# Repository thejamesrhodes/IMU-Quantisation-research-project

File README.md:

# Sheppard MEMS Rate-Register Quantisation Research Project

Custom STM32F723 hardware, firmware and analysis for measuring output-register
quantisation noise in MEMS rate gyroscopes. Specifically gyroscopes that report an
angular-rate register rather than an integrated angle increment.

*This is a pre-publication research project. The preprint is not yet released.
the results, figures and numbers in this repository are working values and are subject to change. 
Nothing here has been peer-reviewed. Preliminary Datasets are available on Zenodo*

---

## Claim

Rate-register quantisation is predicted to appear at a $-1/2$ Allan-deviation
slope and to be absorbed silently into the fitted angle random walk (ARW),
rather than appearing as the $-1$-slope angle-quantisation ("Q") term of IEEE
Std 952, which describes a different output architecture for angle-increment
parts (FOGs, RLGs). This holds regardless of the error's statistics: whether the
quantisation error is PQN-white, deadbanded, or dithered, it enters the rate
and therefore appears inside the fitted ARW instead of appearing as a separable Q.

If that is correct, fitted stochastic-noise parameters depend on the
configuration (output data rate (ODR), full-scale range (FSR), output word
length) at which they were measured, and the $\sqrt{\text{ODR}}$
bandwidth-transfer rule embedded in every mainstream IMU calibration toolchain,
where it is stated as a condition requiring ideal decimation rather than a
validated result, has never been checked for modern high-ODR consumer parts.

**Why this has gone unnoticed.** The transfer rule was safe for the parts it was
developed on. An MPU-6050-class gyro (≈5 mdps/√Hz, 2011) at ±2000 dps / 100 Hz
sits at a dither ratio $\rho = \sigma/\Delta \approx 0.58$, where the
pseudo-quantisation-noise (PQN) model is valid to ~2 %. The ICM-42688-P
(≈2.8 mdps/√Hz, 2020) sits at $\rho \approx 0.32$, where it is not.

The board is named after W. F. Sheppard, whose 1898 paper gave the $-c^2/12$
correction for the variance of grouped data
([DOI](https://doi.org/10.1112/plms/s1-29.1.353)) - the same $\Delta^2/12$ the
whole experiment turns on. The correction reappears in an unexpected place: the
19-bit reference stream is itself a quantiser, and Sheppard's correction must be
applied to it before it can serve as a reference at all.

---

## Project Goals

- Test whether the fitted stochastic-noise parameters of a MEMS IMU transfer
  across ODR and FSR, and return a single configuration-invariant parameter set
  that does.
- Establish that rate-register quantisation presents at the $-1/2$ slope and is
  absorbed into the fitted ARW, distinct from the IEEE-952 angle-quantisation
  term.
- Derive the exact, parameter-free output-quantisation behaviour, governed by
  two quantities: the dither ratio $\rho = \sigma/\Delta$ and the sub-LSB bias
  phase $\mu \bmod \Delta$. Both measurable from a static code histogram with
  no additional hardware.
- Identify which requantisation architecture the output register implements
  (undithered/PQN, truncation, RPDF- or TPDF-dithered) from output data alone,
  validated against bit-exact software-dithered controls.
- Show that no mainstream toolchain (Kalibr, `allan_variance_ros`, …) models
  output-register quantisation or exposes $\rho$ or $\mu$, and document the
  effect size against configuration so a practitioner can locate their own.
- Publish the hardware, firmware, analysis code and a raw-integer-code,
  temperature-logged dataset. A dataset that, on the searches conducted, does
  not currently exist, because public IMU datasets are distributed as calibrated
  floats and the calibration destroys the code lattice.

---

## Project progress

| Item | Status |
| --- | --- |
| Data-logger PCB (4× IMU) Bring up | ✅ Complete |
| Firmware | ✅ Complete |
| Analysis chain ($\sigma$, $\rho$, $\mu$, $\varphi$, $\eta$; Allan; GMWM) | ✅ Complete |
| Exact $\eta(\rho,\varphi)$ theory, closed form | ✅ Validated |
| Primary curve $\eta(\rho)$ | ✅ Measured over a decade of $\rho$ |
| Experimental results vs exact theory | ✅ 0.4 % of range, no free parameters, both specimens |
| Relevance evidence (toolchain guidance, default ODR/FSR) | 🚧 In progress |
| Manuscript | 🚧 Skeleton, not in this repository |
| Preprint | ⏳ Not yet released |

---

## Hardware

|           |                                                            |
| --------- | ---------------------------------------------------------- |
| MCU       | STM32F723ZET6, 32 MHz                                       |
| Sensors   | 2× ICM-42688-P, 1× ISM330DHCX, 1× BMI323, one SPI bus each |
| Storage   | microSD on SDMMC2, exFAT                                    |
| Host link | USB-C on OTG_HS, internal HS PHY                            |
| Power     | 4S NiMH or USB-C                                            |

---

## Repository structure

```
GMWM Software/                 STM32CubeIDE firmware project + host Python
  Core/                          application sources
  tools/                         console, analysis, figures
GMWM Electronics/              KiCad 10 — data-logger PCB
Array Electronics ICM42688P/   KiCad 10 — ICM-42688-P board
Array Software ICM42688P/      firmware for the ICM-42688-P board
Test Datasets/                 records (gitignored; archived to Zenodo)
zenodo/                        dataset deposit build system
```

---

## Running it

```
pip install pyserial numpy matplotlib
python "GMWM Software/tools/sheppard_console.py"
```

The console is a GUI with five tabs: a terminal, the SD-card browser, the
campaign-plan editor, an analysis runner, and a figure viewer that renders the
plots in-app. It finds the board by USB ID rather than COM port and reconnects
on its own when the board resets.

Everything it does is also available from the command line, and the panel prints
the exact command before it runs it, so a result in the GUI and a result in a
terminal are the same result.

```
python analyse.py summary "../../Test Datasets" -o "../../Test Datasets/summary.csv" --fast
python figures.py "../../Test Datasets/summary.csv" -o "../../Figures"
python offset_fit.py "../../Test Datasets" --glob "*ph_k*.sdat"
```

---

## Flashing without an ST-LINK

The board reflashes itself over the same USB-C cable that carries the console.

Run `sheppard_selftest.py` once before trusting the flasher. It feeds the board
bad data five ways and checks each one is refused with flash untouched. Nothing
in it can erase the board.

SWD recovery is always there:

```
STM32_Programmer_CLI -c port=SWD mode=UR -e all -w "Debug/GMWM STM32.elf" -v -rst
```

---

## Status

94 records, two specimens, three axes. The register's architecture is identified
(truncation, bit-exact); $\eta(\rho)$ is measured over a decade of $\rho$; and a
controlled phase sweep tracks the exact theory to **0.4 % of its range with no
free parameters — on both specimens independently**. Repeatability is measured
at $\sigma_\eta = 0.0065$, so the theory is good to about twice the noise floor
of the apparatus.

The manuscript is a skeleton and is not held in this repository. The bench
work the preprint needs is
done; what remains is desk work — the relevance evidence, the software-dither
sweep, and the writing.

---

## Preprint and data

The preprint is not yet released. A manuscript is in preparation and is
intended for submission to a measurement-science journal (IOP
*Measurement Science and Technology*); this section will carry the preprint DOI
when it is public.

Campaign data is archived to Zenodo and is not held in this repository:

> Rhodes, J. (2026). *Paired 16-bit and 19-bit output records from two
> ICM-42688-P MEMS gyroscopes across output-rate and sub-LSB bias-offset
> sweeps* [Data set]. Zenodo. <https://doi.org/10.5281/zenodo.22860515>

---

## Conventions

SI units. LaTeX for maths. Campaign data goes to Zenodo with a DOI, not into
this repository.

The gyroscope's high-resolution FIFO field is 20 bits wide, of which 19 are
significant at ±2000 °/s full scale — the field's least significant bit is
always zero. All resolutions in this repository and in the dataset are quoted
on the 19-bit convention, so the reference lattice step is $\Delta' = \Delta/8$
and the register word is `gyro19 >> 3`.

---

## Licence

MIT — see `LICENSE`. The dataset is licensed separately under CC-BY-4.0.

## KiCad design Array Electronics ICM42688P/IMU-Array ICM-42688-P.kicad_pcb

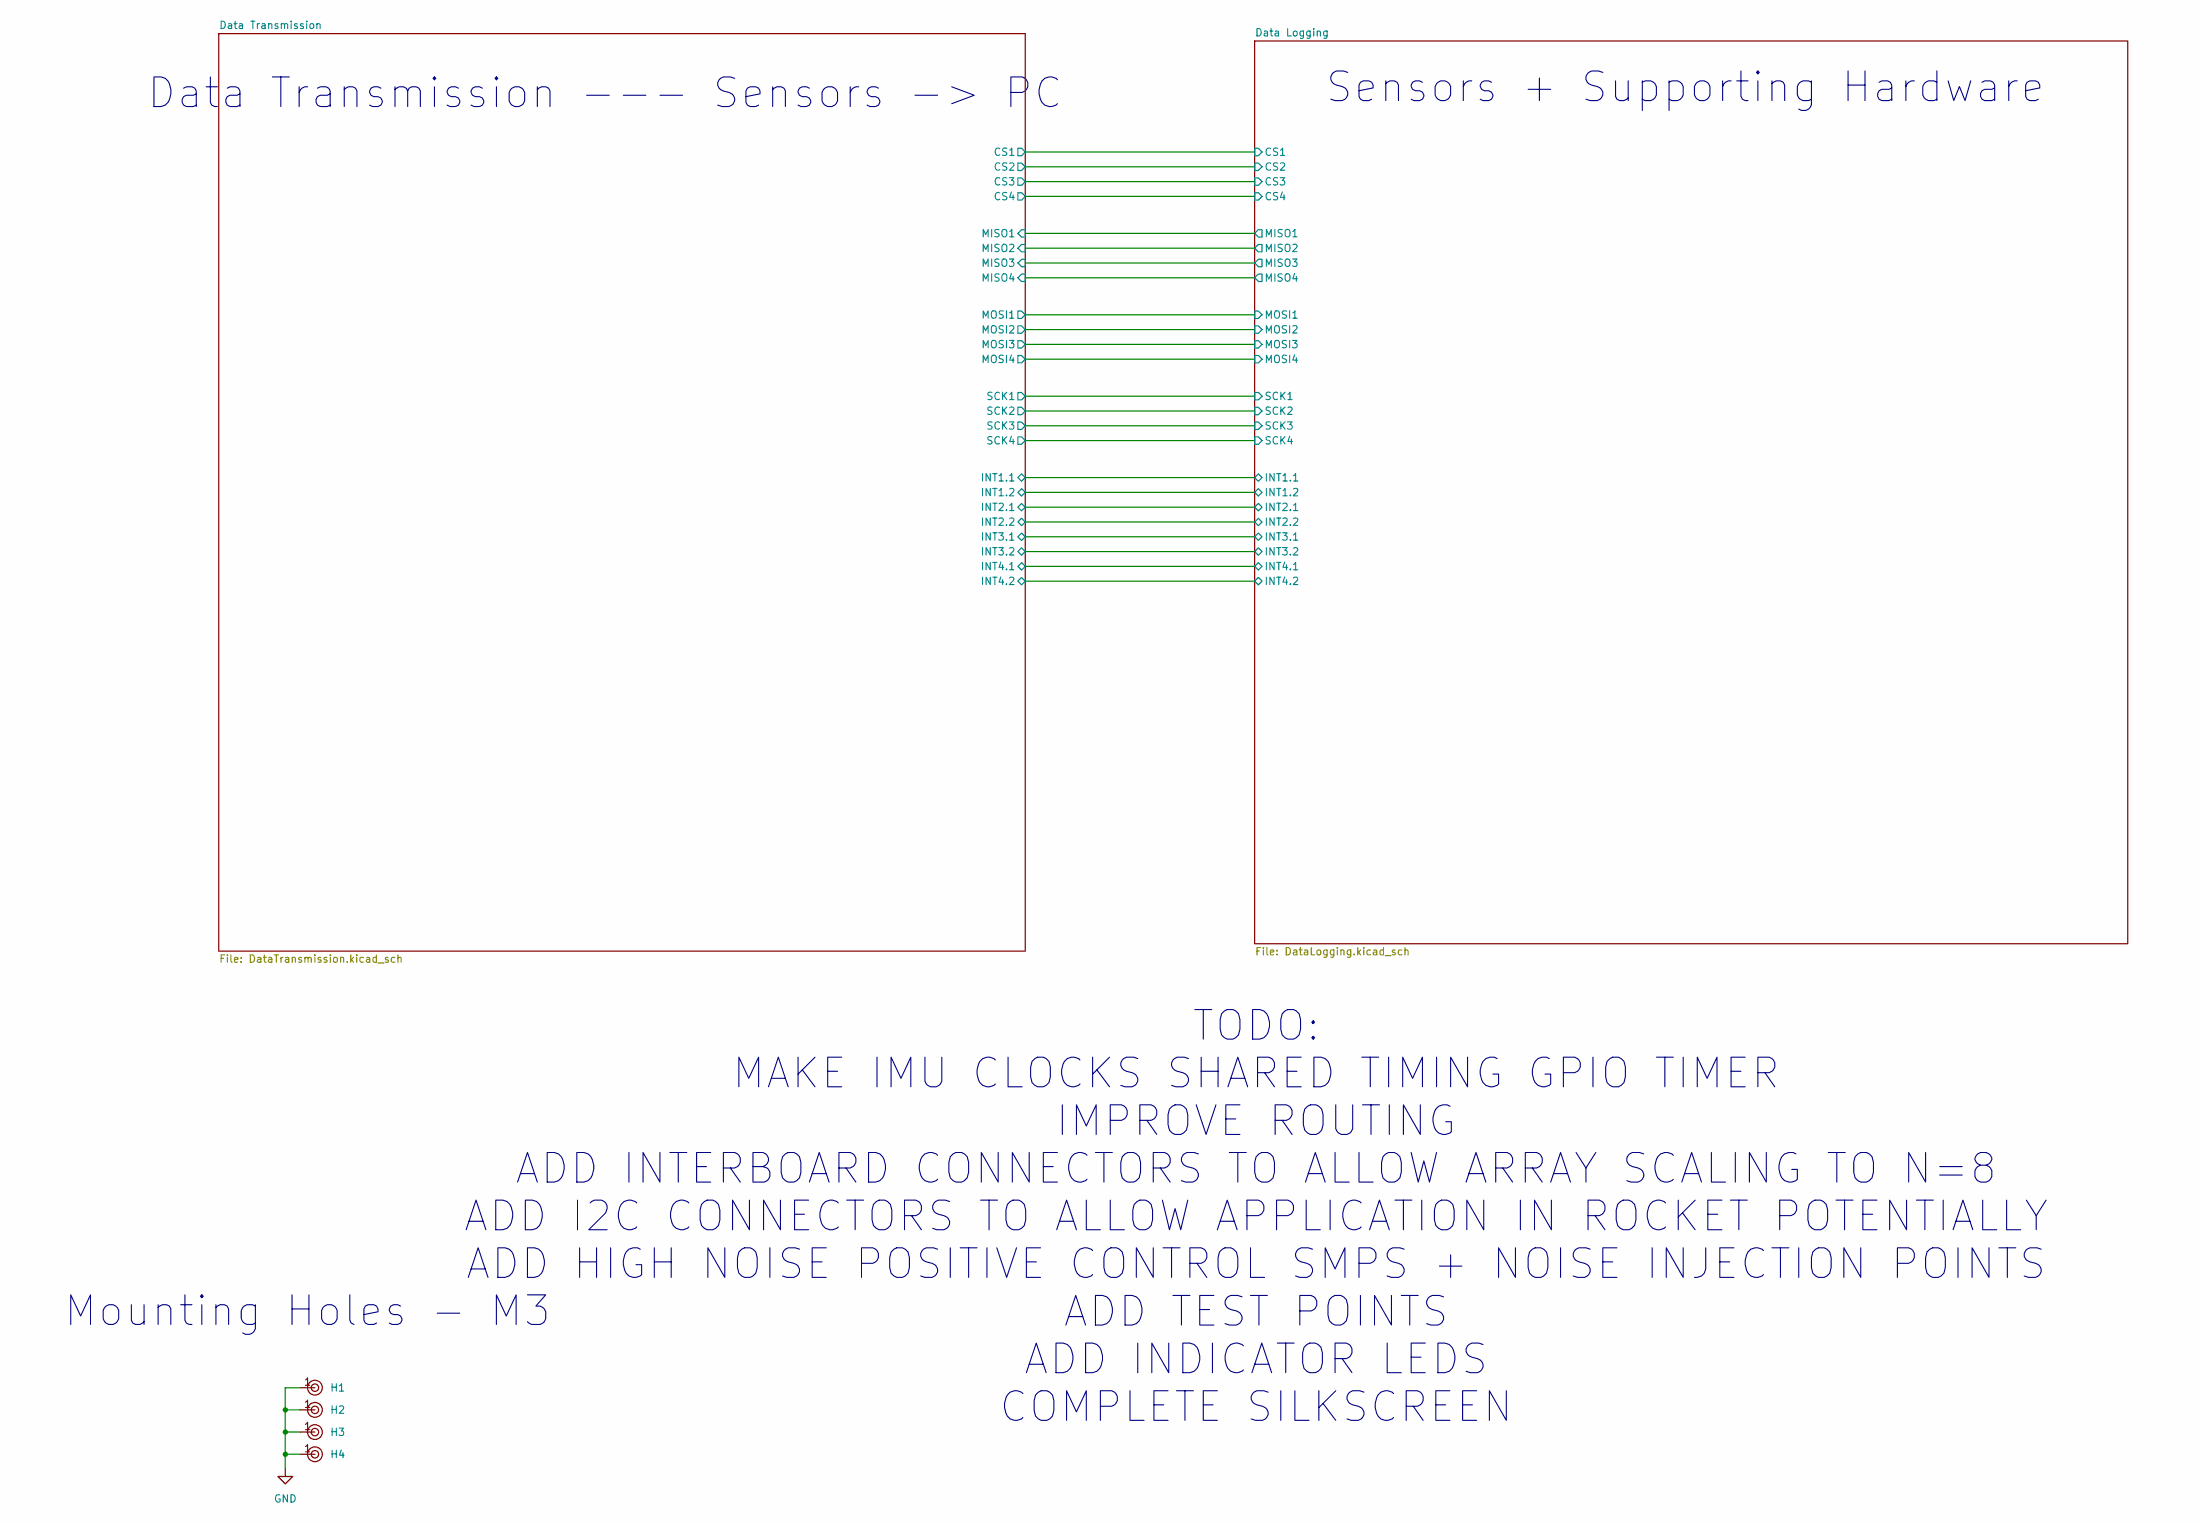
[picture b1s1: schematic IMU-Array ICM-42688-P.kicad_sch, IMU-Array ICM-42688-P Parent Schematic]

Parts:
H1, H2, H3, H4: Hole, 3mm

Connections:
GND: H1.1, H2.1, H3.1, H4.1; also elsewhere on the board

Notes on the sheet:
Sensors + Supporting Hardware
TODO: MAKE IMU CLOCKS SHARED TIMING GPIO TIMER IMPROVE ROUTING ADD INTERBOARD CONNECTORS TO ALLOW ARRAY SCALING TO N=8 ADD I2C CONNECTORS TO ALLOW APPLICATION IN ROCKET POTENTIALLY ADD HIGH NOISE POSITIVE CONTROL SMPS + NOISE INJECTION POINTS ADD TEST POINTS ADD INDICATOR LEDS COMPLETE SILKSCREEN
Data Transmission --- Sensors -> PC
Mounting Holes - M3

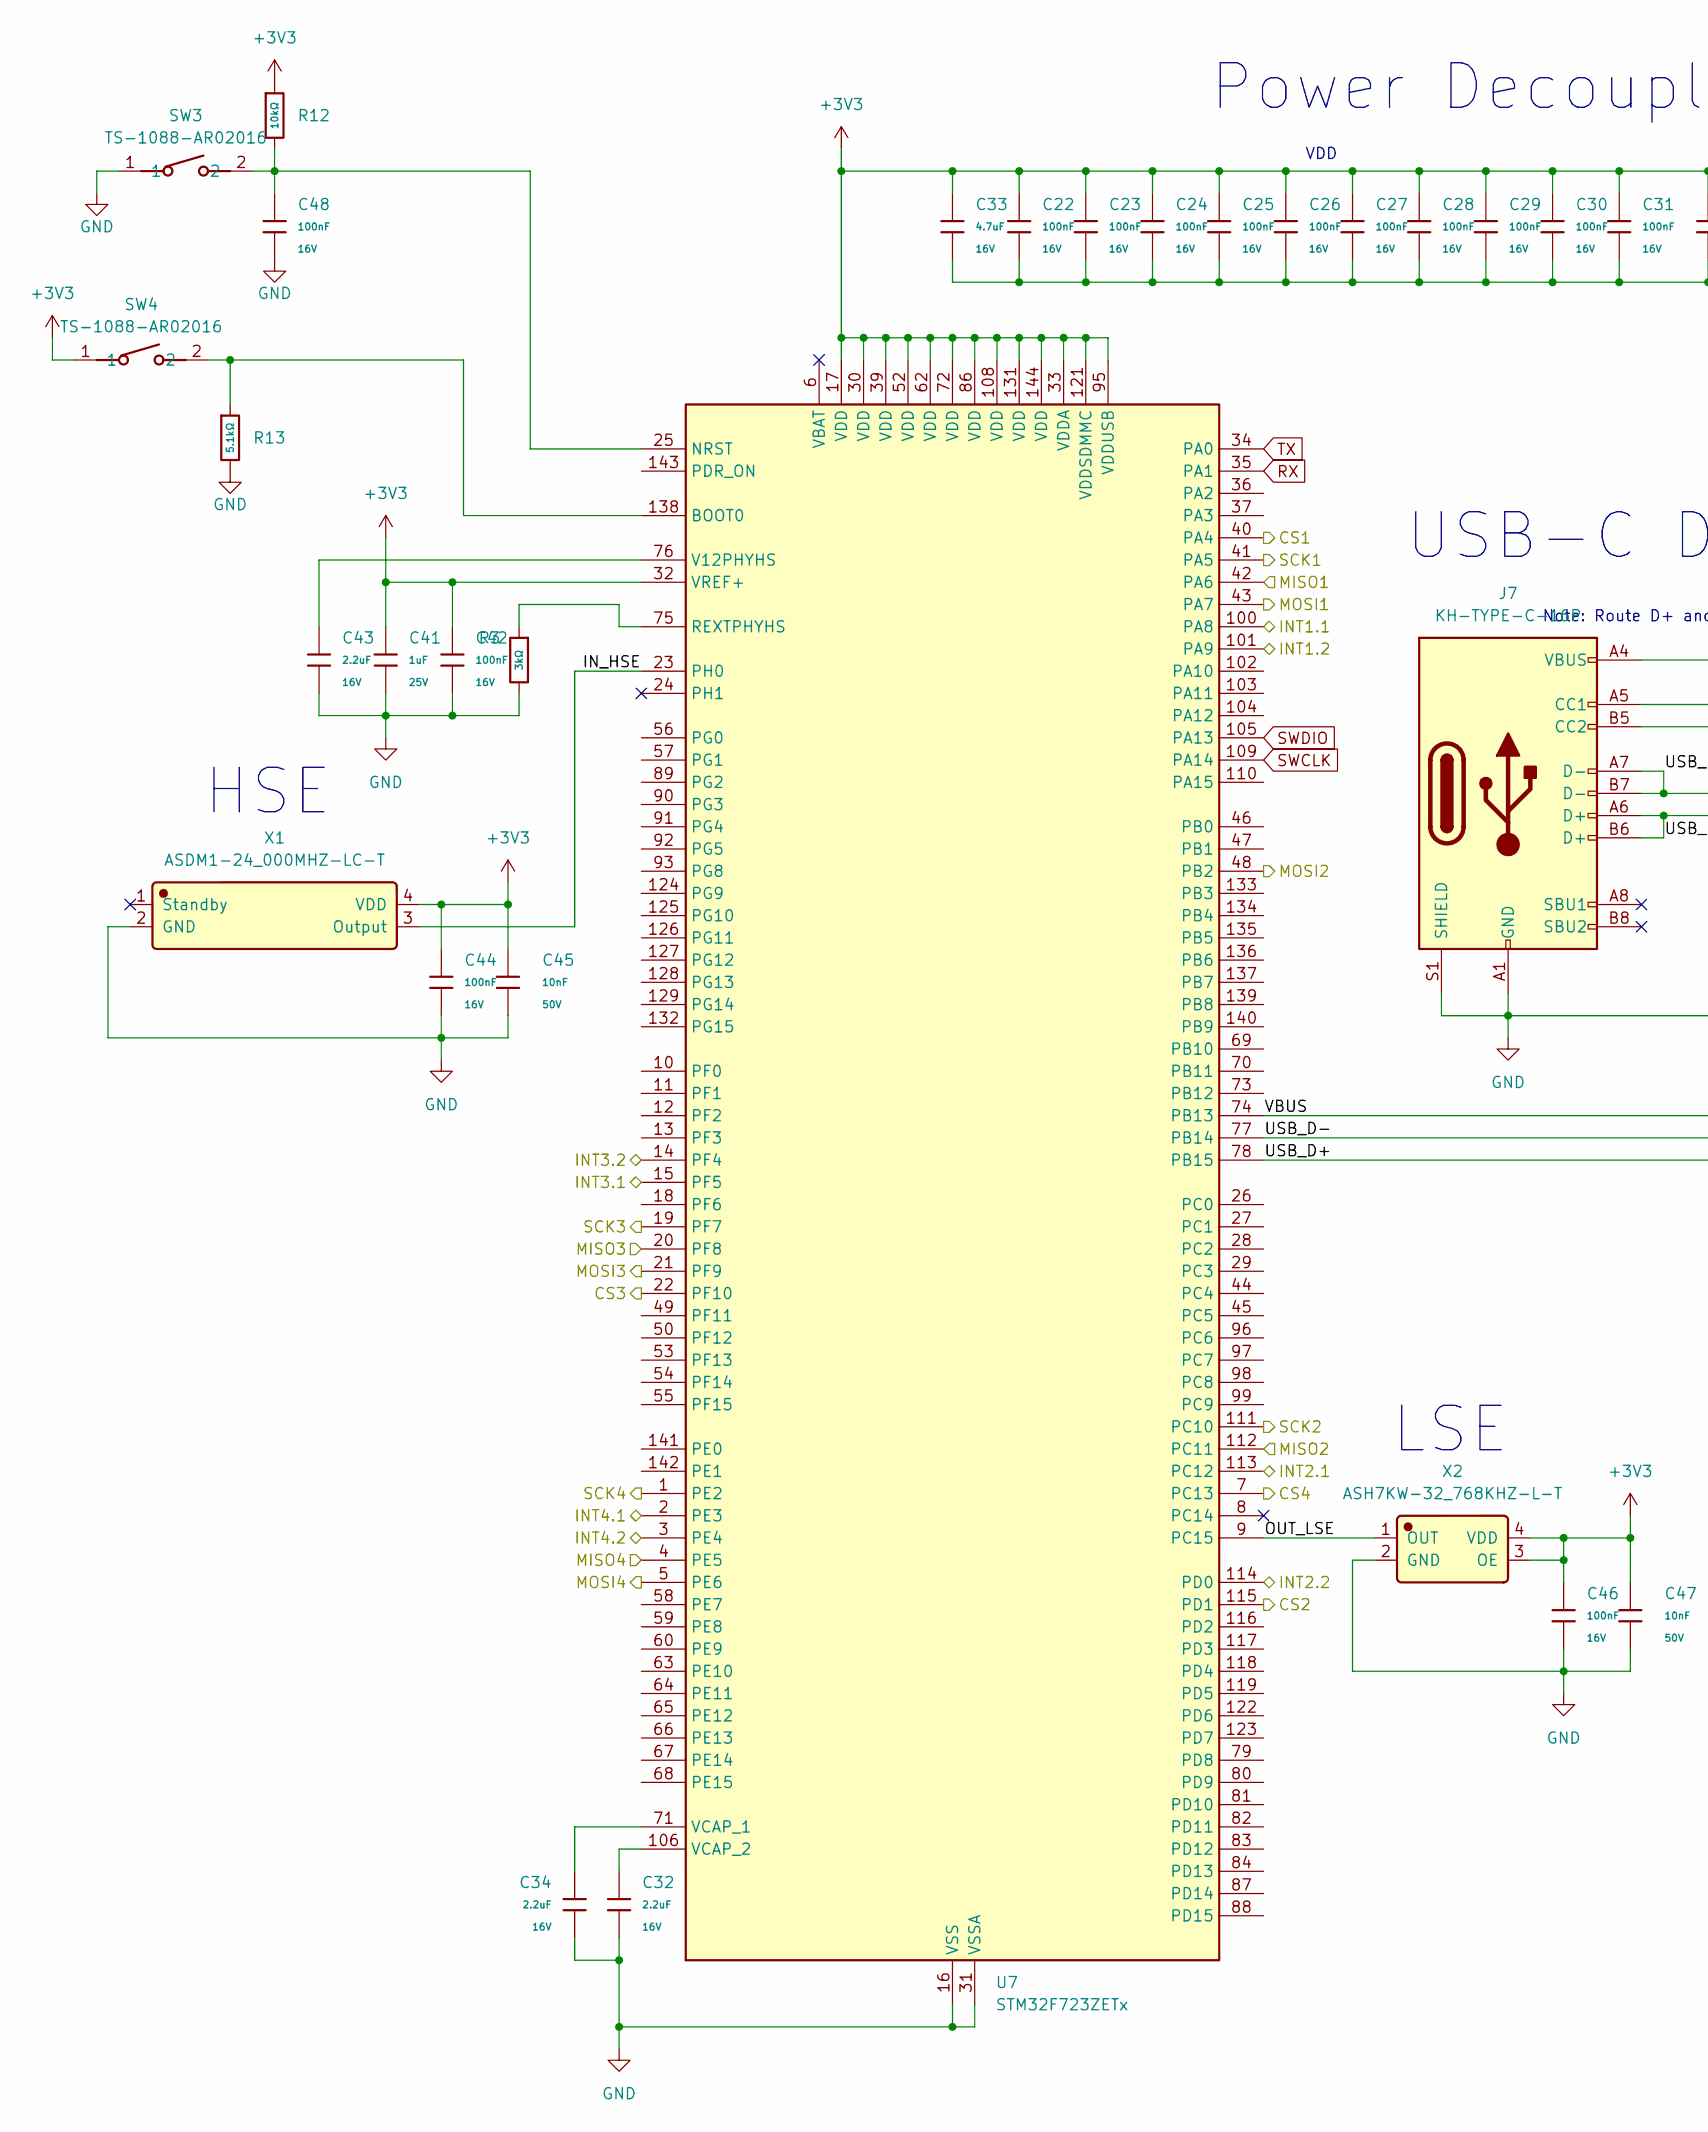
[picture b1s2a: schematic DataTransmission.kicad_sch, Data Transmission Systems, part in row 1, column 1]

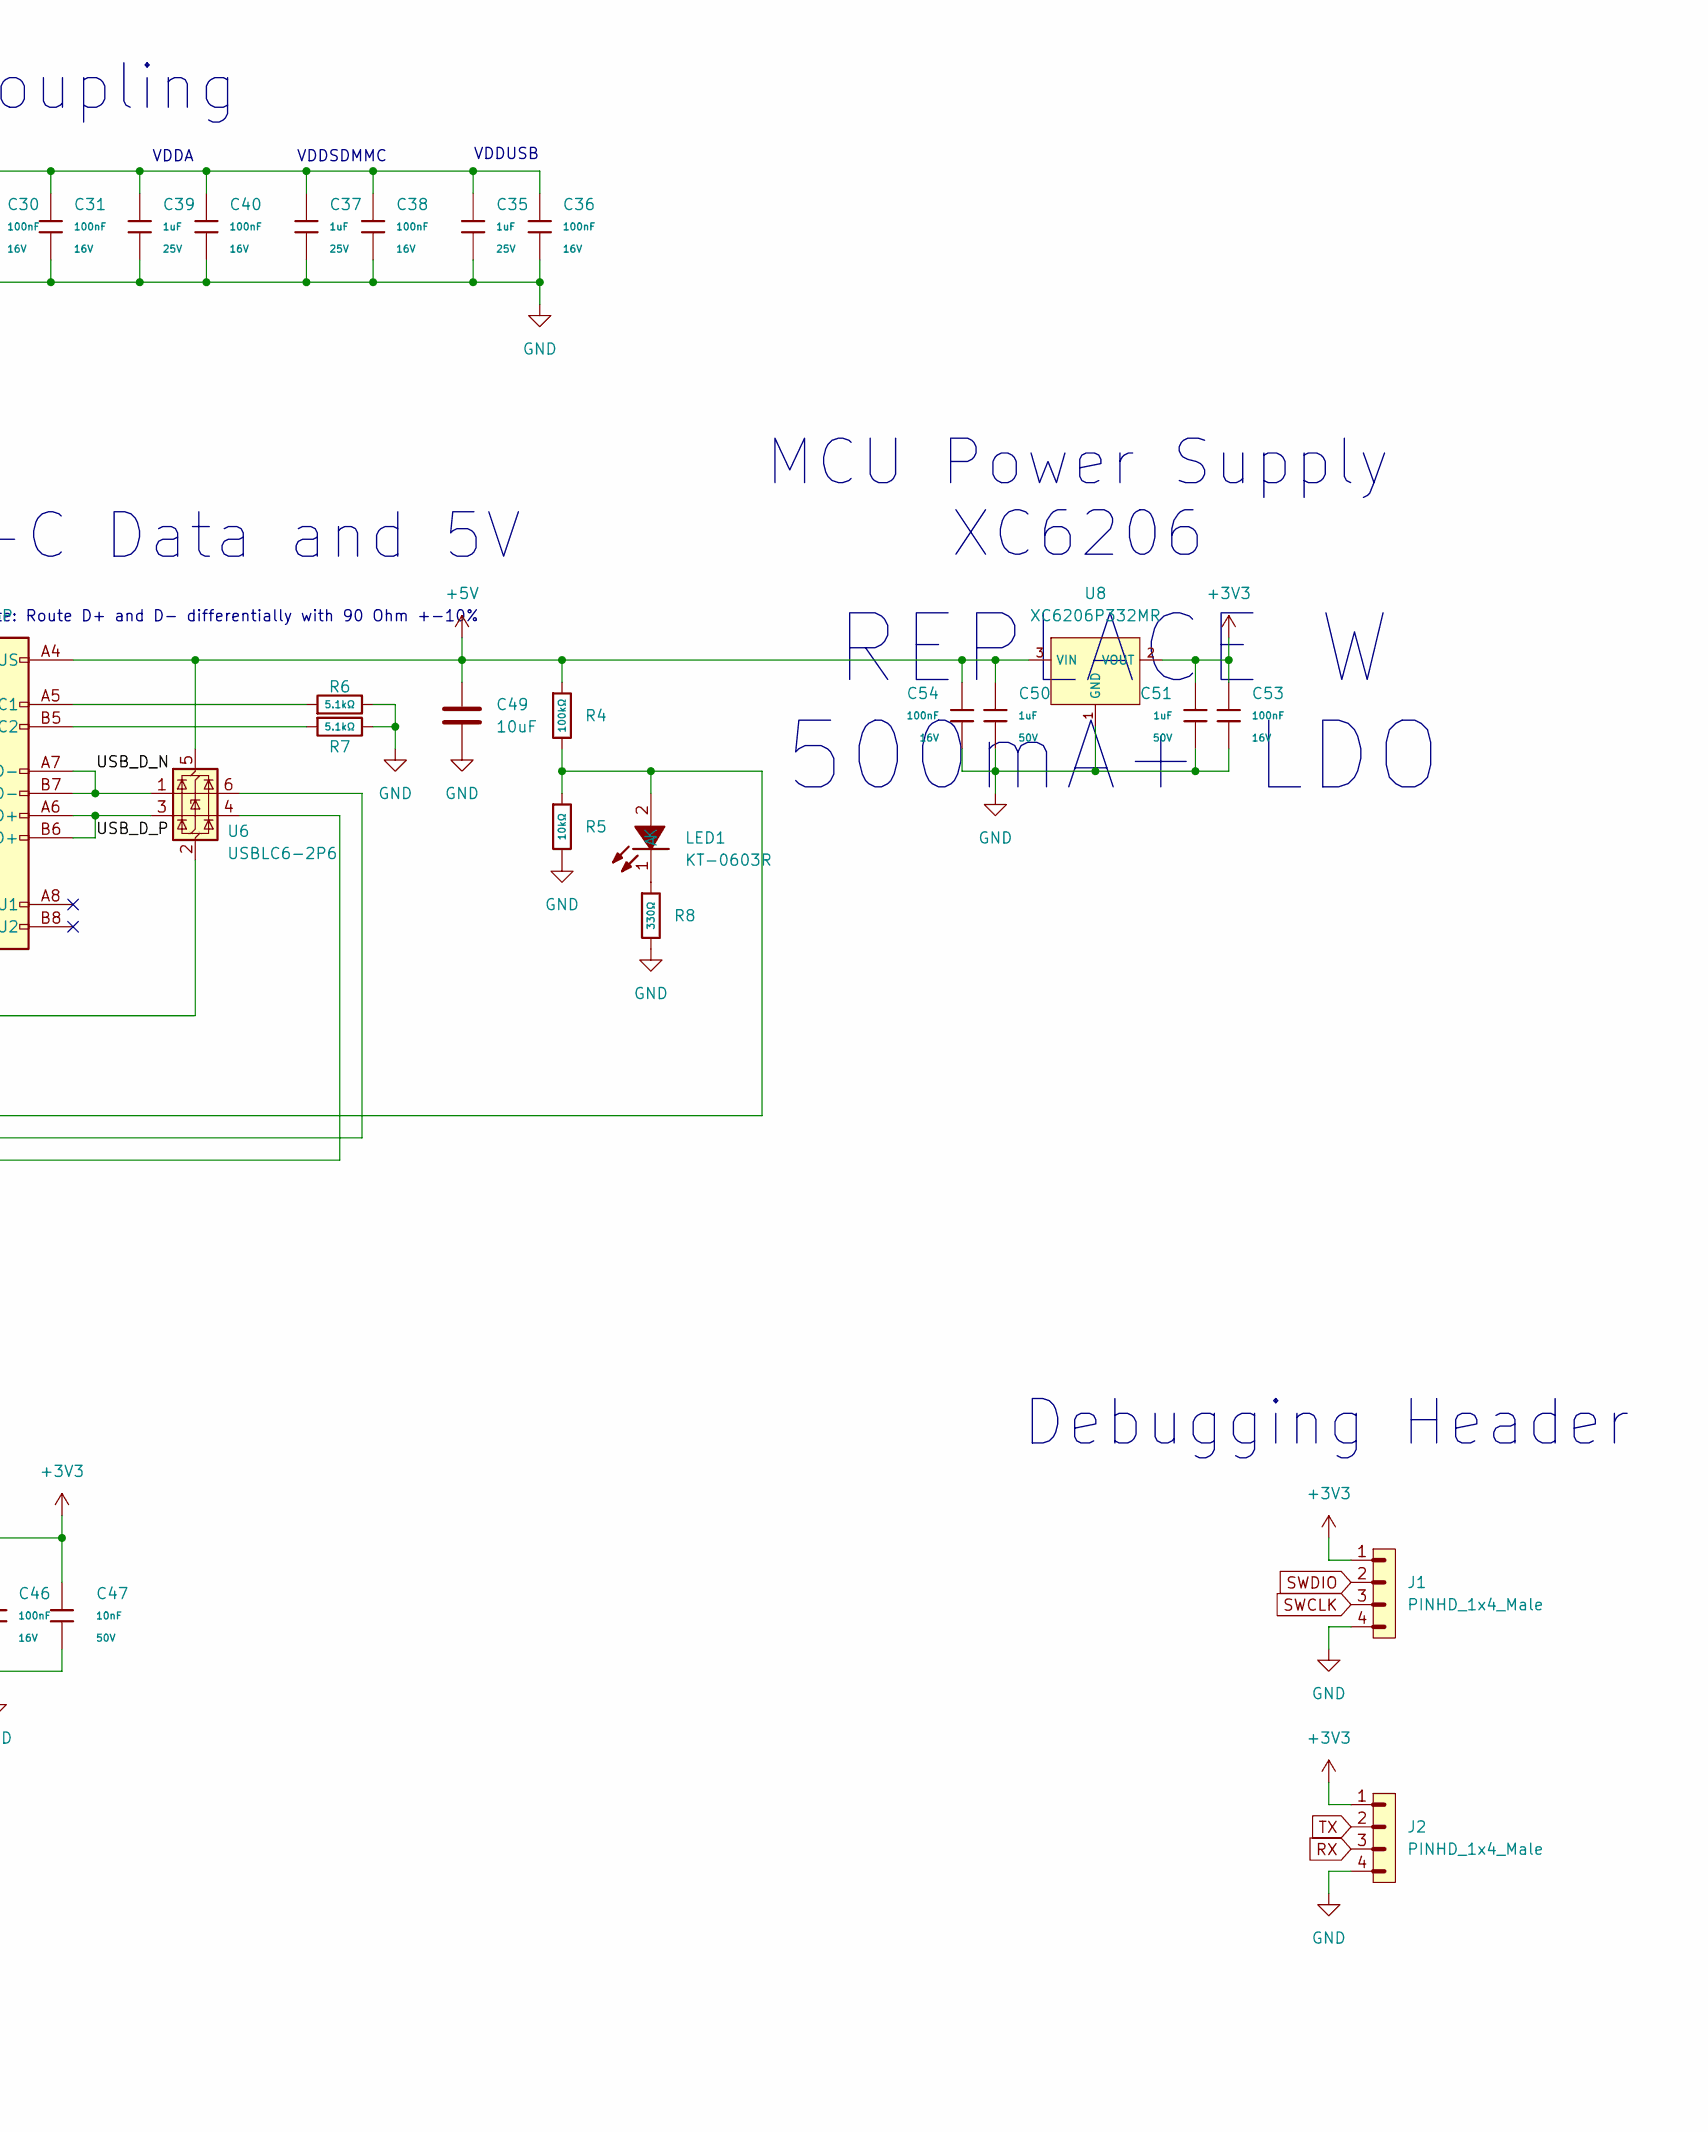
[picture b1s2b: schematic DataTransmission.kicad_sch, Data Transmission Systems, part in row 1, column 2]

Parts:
C22, C23, C24, C25, C26, C27, C28, C29, C30, C31, C36, C38, C40, C42, C44, C46, C48, C53, C54: 100nF; C_0402; Voltage Rated 16V; Tolerance ±10%; Part CL05B104KO5NNNC; LCSC C1525
C32, C34, C43: 2.2uF; C_0603; Voltage Rated 16V; Tolerance ±10%; Part CL10A225KO8NNNC; LCSC C23630
C33: 4.7uF; C_0603; Voltage Rated 16V; Tolerance ±10%; Part CL10A475KO8NNNC; LCSC C19666
C35, C37, C39, C41: 1uF; C_0402; Voltage Rated 25V; Tolerance ±10%; Part CL05A105KA5NQNC; LCSC C52923
C45, C47: 10nF; C_0402; Voltage Rated 50V; Tolerance ±10%; Part CL05B103KB5NNNC; LCSC C15195
C49: 10uF; C_0603
C50, C51: 1uF; C_0603; Voltage Rated 50V; Tolerance ±10%; Part CL10A105KB8NNNC; LCSC C15849
J1, J2: PINHD_1x4_Male; PinHeader_1x04_P2.54mm_Vertical
J7: KH-TYPE-C-16P
LED1: KT-0603R; Manufacturer Part KT-0603R; LCSC C2286
R3: 3kΩ; R_0603; Overload Voltage (Max) 75V; Tolerance ±1%; Part 0603WAF3001T5E; LCSC C4211
R4: 100kΩ; R_0402; Overload Voltage (Max) 50V; Tolerance ±1%; Part 0402WGF1003TCE; LCSC C25741
R5, R12: 10kΩ; R_0402; Overload Voltage (Max) 50V; Tolerance ±1%; Part 0402WGF1002TCE; LCSC C25744
R6, R7, R13: 5.1kΩ; R_0402; Overload Voltage (Max) 50V; Tolerance ±1%; Part 0402WGF5101TCE; LCSC C25905
R8: 330Ω; R_0402; Overload Voltage (Max) 50V; Tolerance ±1%; Part 0402WGF3300TCE; LCSC C25104
SW3, SW4: TS-1088-AR02016; Manufacturer Part TS-1088-AR02016; LCSC C720477
U6: USBLC6-2P6; SOT-666
U7: STM32F723ZETx; LQFP-144_20x20mm_P0.5mm
U8: XC6206P332MR; SOT-23-3_L2.9-W1.6-P1.90-LS2.8-BR; Output Voltage 3.3V; Dropout Voltage 680mV@(100mA); Part XC6206P332MR-G; LCSC C5446
X1: ASDM1-24_000MHZ-LC-T; Manufacturer Part ASDM1-24.000MHZ-LC-T; LCSC C1987235
X2: ASH7KW-32_768KHZ-L-T; Manufacturer Part ASH7KW-32.768KHZ-L-T; LCSC C6277865

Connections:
+3V3: C22.1, C23.1, C24.1, C25.1, C26.1, C27.1, C28.1, C29.1, C30.1, C31.1, C33.1, C35.1, C36.1, C37.1, C38.1, C39.1, C40.1, C41.1, C42.1, C44.1, C45.1, C46.1, C47.1, C51.1, C53.1, J1.1, J2.1, R12.1, SW4.1, U7.17 (VDD), U7.30 (VDD), U7.32 (VREF+), U7.33 (VDDA), U7.39 (VDD), U7.52 (VDD), U7.62 (VDD), U7.72 (VDD), U7.86 (VDD), U7.95 (VDDUSB), U7.108 (VDD), U7.121 (VDDSDMMC), U7.131 (VDD), U7.144 (VDD), U8.2 (VOUT), X1.4 (VDD), X2.3 (OE), X2.4 (VDD)
+5V: C49.1, C50.1, C54.1, J7.A4 (VBUS), J7.A9 (VBUS), J7.B4 (VBUS), J7.B9 (VBUS), R4.1, U6.5 (VBUS), U8.3 (VIN); also elsewhere on the board
/Data Logging/CS1: U7.40 (PA4); also elsewhere on the board
/Data Logging/CS2: U7.115 (PD1); also elsewhere on the board
/Data Logging/CS3: U7.22 (PF10); also elsewhere on the board
/Data Logging/CS4: U7.7 (PC13); also elsewhere on the board
/Data Logging/INT1.1: U7.100 (PA8); also elsewhere on the board
/Data Logging/INT1.2: U7.101 (PA9); also elsewhere on the board
/Data Logging/INT2.1: U7.113 (PC12); also elsewhere on the board
/Data Logging/INT2.2: U7.114 (PD0); also elsewhere on the board
/Data Logging/INT3.1: U7.15 (PF5); also elsewhere on the board
/Data Logging/INT3.2: U7.14 (PF4); also elsewhere on the board
/Data Logging/INT4.1: U7.2 (PE3); also elsewhere on the board
/Data Logging/INT4.2: U7.3 (PE4); also elsewhere on the board
/Data Logging/MISO1: U7.42 (PA6); also elsewhere on the board
/Data Logging/MISO2: U7.112 (PC11); also elsewhere on the board
/Data Logging/MISO3: U7.20 (PF8); also elsewhere on the board
/Data Logging/MISO4: U7.4 (PE5); also elsewhere on the board
/Data Logging/MOSI1: U7.43 (PA7); also elsewhere on the board
/Data Logging/MOSI2: U7.48 (PB2); also elsewhere on the board
/Data Logging/MOSI3: U7.21 (PF9); also elsewhere on the board
/Data Logging/MOSI4: U7.5 (PE6); also elsewhere on the board
/Data Logging/SCK1: U7.41 (PA5); also elsewhere on the board
/Data Logging/SCK2: U7.111 (PC10); also elsewhere on the board
/Data Logging/SCK3: U7.19 (PF7); also elsewhere on the board
/Data Logging/SCK4: U7.1 (PE2); also elsewhere on the board
/Data Transmission/IN_HSE: U7.23 (PH0), X1.3 (Output)
/Data Transmission/OUT_LSE: U7.9 (PC15), X2.1 (OUT)
/Data Transmission/USB_D+: U6.4 (I/O2), U7.78 (PB15)
/Data Transmission/USB_D-: U6.6 (I/O1), U7.77 (PB14)
/Data Transmission/USB_D_N: J7.A7 (D-), J7.B7 (D-), U6.1 (I/O1)
/Data Transmission/USB_D_P: J7.A6 (D+), J7.B6 (D+), U6.3 (I/O2)
/Data Transmission/VBUS: LED1.2 (A), R4.2, R5.1, U7.74 (PB13)
GND: C22.2, C23.2, C24.2, C25.2, C26.2, C27.2, C28.2, C29.2, C30.2, C31.2, C32.2, C33.2, C34.2, C35.2, C36.2, C37.2, C38.2, C39.2, C40.2, C41.2, C42.2, C43.2, C44.2, C45.2, C46.2, C47.2, C48.2, C49.2, C50.2, C51.2, C53.2, C54.2, J1.4, J2.4, J7.A1 (GND), J7.A12 (GND), J7.B1 (GND), J7.B12 (GND), J7.S1 (SHIELD), R3.2, R5.2, R6.2, R7.2, R8.2, R13.2, SW3.1, U6.2 (GND), U7.16 (VSS), U7.31 (VSSA), U7.38 (VSS), U7.51 (VSS), U7.61 (VSS), U7.85 (VSS), U7.94 (VSS), U7.107 (VSS), U7.120 (VSS), U7.130 (VSS), U8.1 (GND), X1.2 (GND), X2.2 (GND); also elsewhere on the board
unnamed: J7.A5 (CC1), R6.1
unnamed: J7.B5 (CC2), R7.1
unnamed: LED1.1 (K), R8.1
unnamed: R13.1, SW4.2, U7.138 (BOOT0)
unnamed: C48.1, R12.2, SW3.2, U7.25 (NRST)
unnamed: R3.1, U7.75 (REXTPHYHS)
unnamed: C43.1, U7.76 (V12PHYHS)
unnamed: C34.1, U7.71 (VCAP_1)
unnamed: C32.1, U7.106 (VCAP_2)
RX: J2.3, U7.35 (PA1)
SWCLK: J1.3, U7.109 (PA14)
SWDIO: J1.2, U7.105 (PA13)
TX: J2.2, U7.34 (PA0)

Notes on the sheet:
VDDA
HSE
VDDUSB
VDDSDMMC
VDD
REPLACE W 500mA+ LDO
Debugging Header
MCU Power Supply XC6206
LSE
USB-C Data and 5V
Note: Route D+ and D- differentially with 90 Ohm +-10%
Power Decoupling

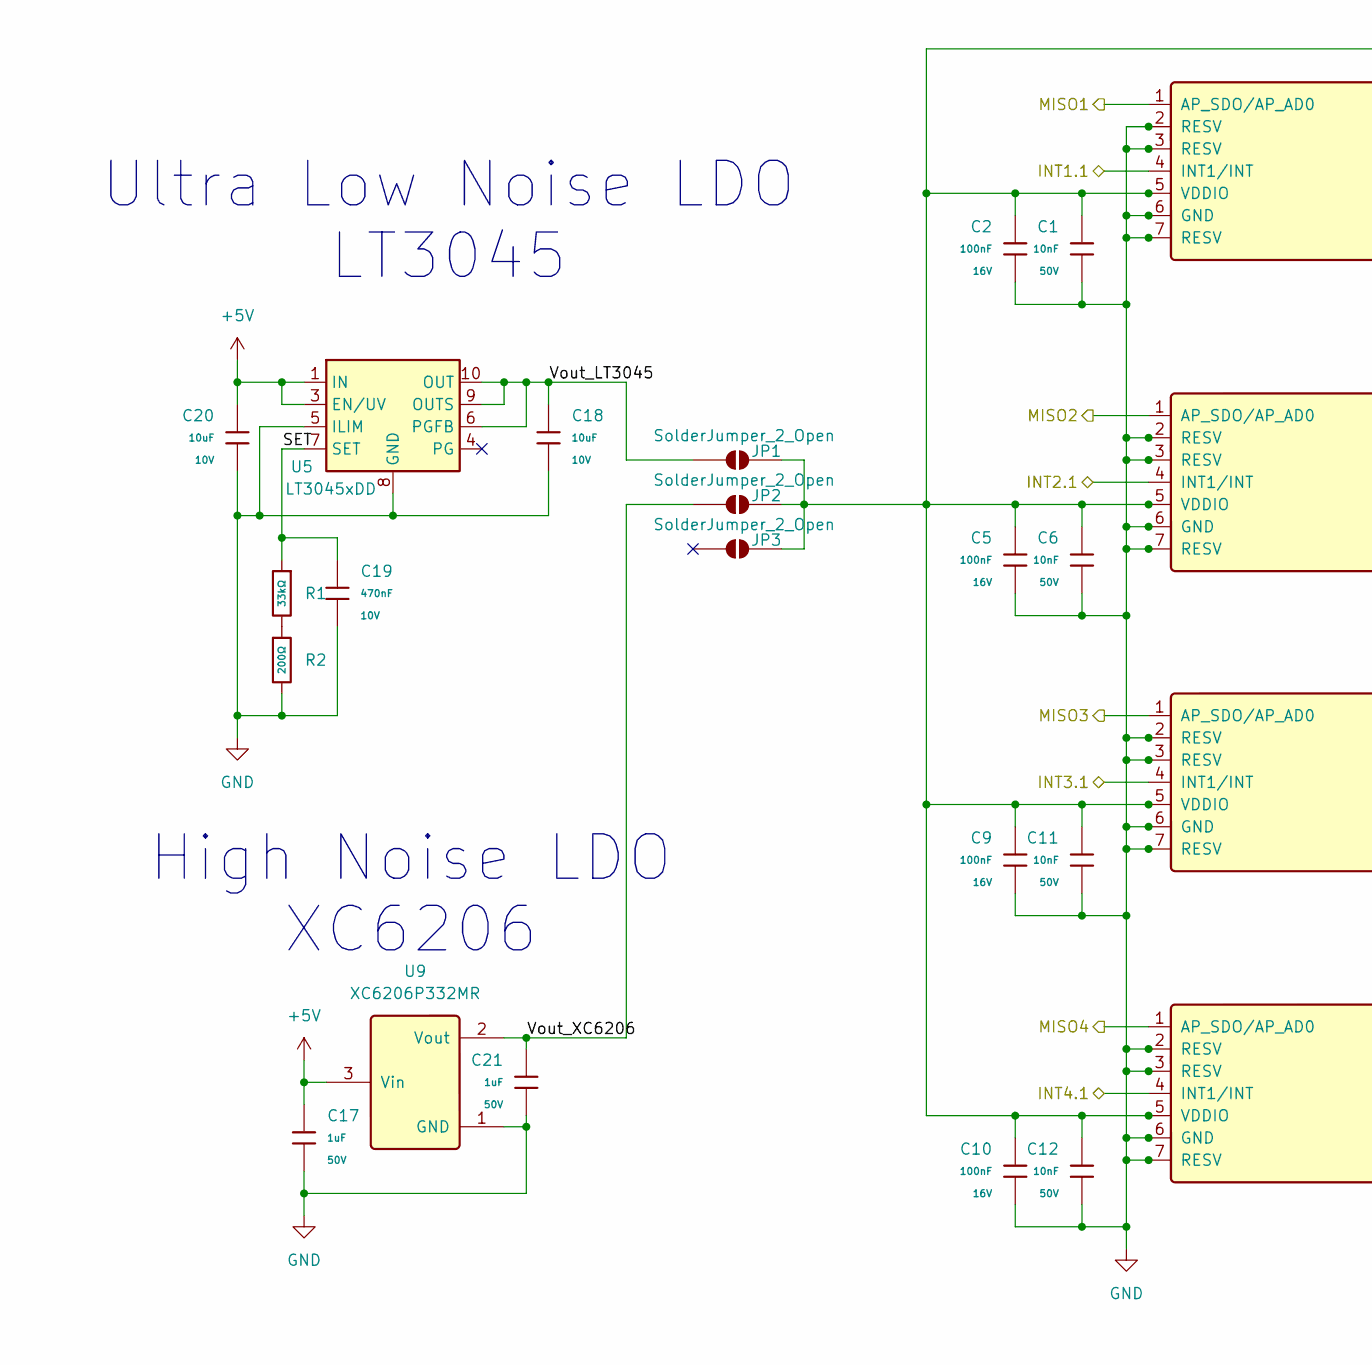
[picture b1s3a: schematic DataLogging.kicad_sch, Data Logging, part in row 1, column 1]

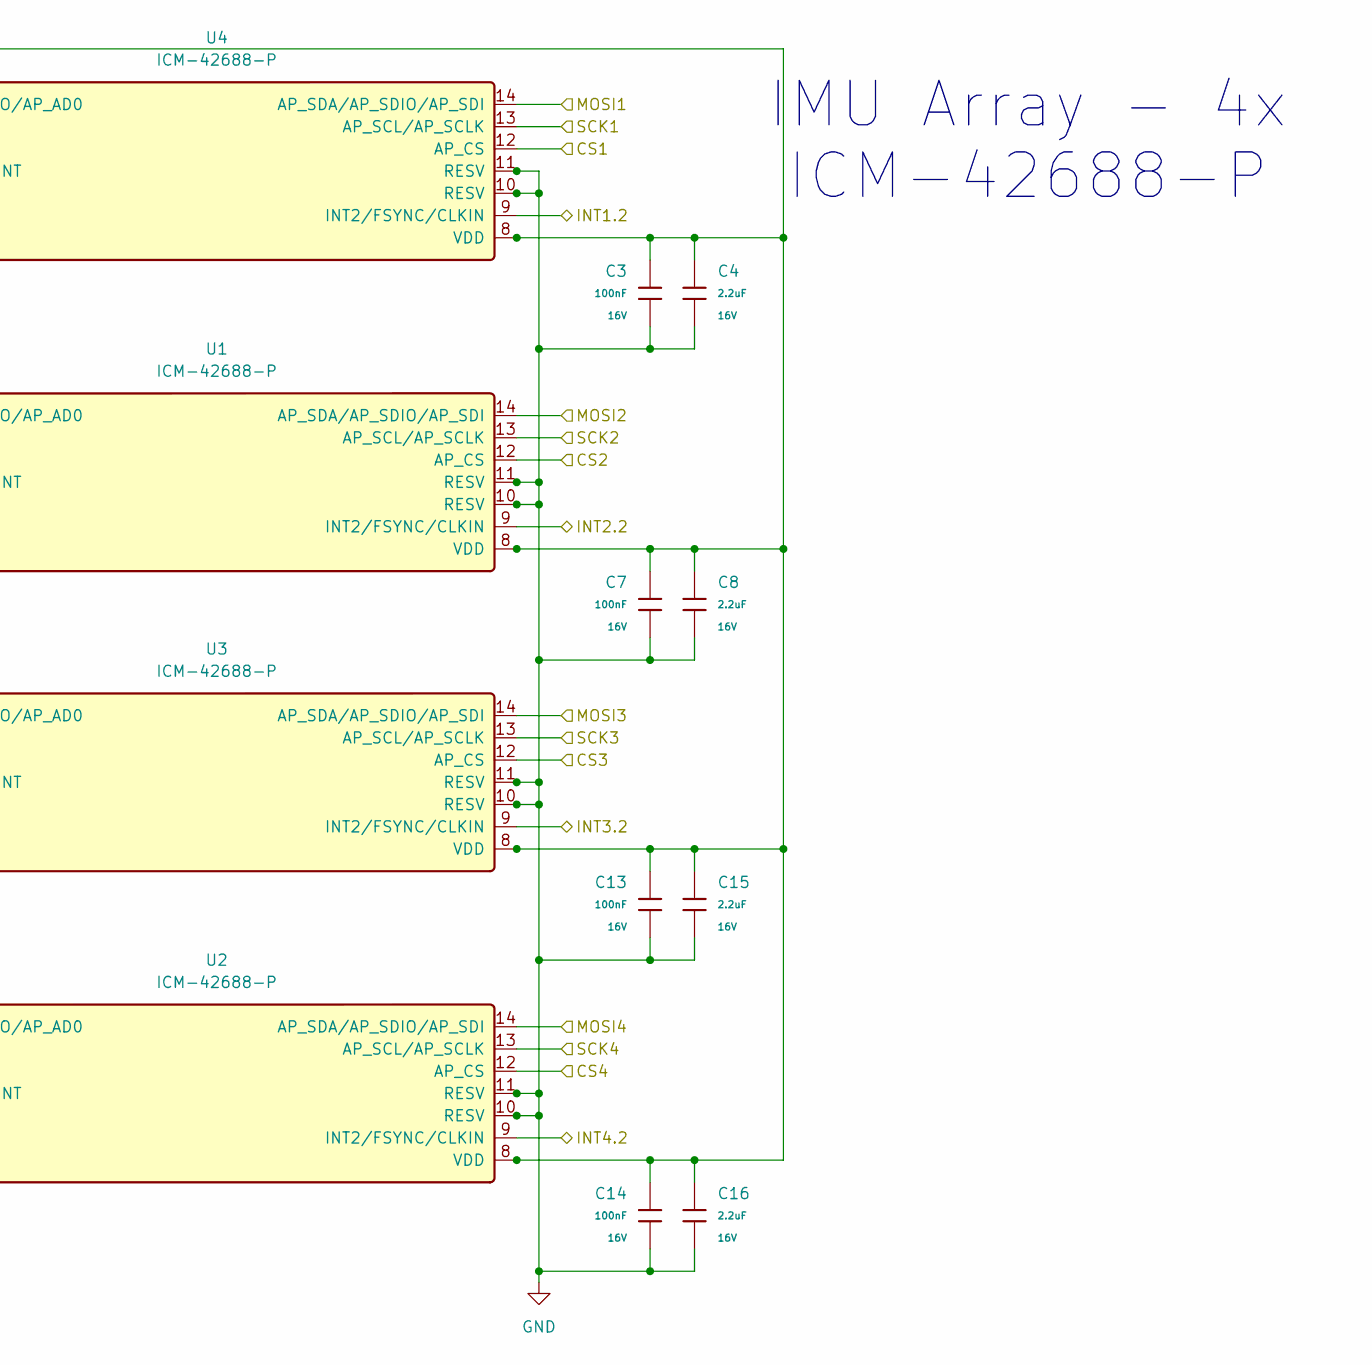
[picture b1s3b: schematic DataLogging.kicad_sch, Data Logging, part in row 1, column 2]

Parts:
C1, C6, C11, C12: 10nF; C_0402; Voltage Rated 50V; Tolerance ±10%; Part CL05B103KB5NNNC; LCSC C15195
C2, C3, C5, C7, C9, C10, C13, C14: 100nF; C_0402; Voltage Rated 16V; Tolerance ±10%; Part CL05B104KO5NNNC; LCSC C1525
C4, C8, C15, C16: 2.2uF; C_0603; Voltage Rated 16V; Tolerance ±10%; Part CL10A225KO8NNNC; LCSC C23630
C17, C21: 1uF; C_0603; Voltage Rated 50V; Tolerance ±10%; Part CL10A105KB8NNNC; LCSC C15849
C18, C20: 10uF; C_0603; Voltage Rated 10V; Tolerance ±10%; Part CL10A106KP8NNNC; LCSC C19702
C19: 470nF; C_0402; Voltage Rated 10V; Tolerance ±10%; Part CL05A474KP5NNNC; LCSC C47339
JP1, JP2, JP3: SolderJumper_2_Open; SolderJumper-2_P1.3mm_Open_TrianglePad1.0x1.5mm
R1: 33kΩ; R_0402; Overload Voltage (Max) 50V; Tolerance ±1%; Part 0402WGF3302TCE; LCSC C25779
R2: 200Ω; R_0402; Overload Voltage (Max) 50V; Tolerance ±1%; Part 0402WGF2000TCE; LCSC C25087
U1, U2, U3, U4: ICM-42688-P; Manufacturer Part ICM-42688-P; LCSC C1850418
U5: LT3045xDD; DFN-10-1EP_3x3mm_P0.5mm_EP1.65x2.38mm
U9: XC6206P332MR; Manufacturer Part XC6206P332MR-G; LCSC C5446

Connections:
+5V: C17.1, C20.1, U5.1 (IN), U5.2 (IN), U5.3 (EN/UV), U9.3 (Vin); also elsewhere on the board
/Data Logging/CS1: U4.12 (AP_CS); also elsewhere on the board
/Data Logging/CS2: U1.12 (AP_CS); also elsewhere on the board
/Data Logging/CS3: U3.12 (AP_CS); also elsewhere on the board
/Data Logging/CS4: U2.12 (AP_CS); also elsewhere on the board
/Data Logging/INT1.1: U4.4 (INT1/INT); also elsewhere on the board
/Data Logging/INT1.2: U4.9 (INT2/FSYNC/CLKIN); also elsewhere on the board
/Data Logging/INT2.1: U1.4 (INT1/INT); also elsewhere on the board
/Data Logging/INT2.2: U1.9 (INT2/FSYNC/CLKIN); also elsewhere on the board
/Data Logging/INT3.1: U3.4 (INT1/INT); also elsewhere on the board
/Data Logging/INT3.2: U3.9 (INT2/FSYNC/CLKIN); also elsewhere on the board
/Data Logging/INT4.1: U2.4 (INT1/INT); also elsewhere on the board
/Data Logging/INT4.2: U2.9 (INT2/FSYNC/CLKIN); also elsewhere on the board
/Data Logging/MISO1: U4.1 (AP_SDO/AP_AD0); also elsewhere on the board
/Data Logging/MISO2: U1.1 (AP_SDO/AP_AD0); also elsewhere on the board
/Data Logging/MISO3: U3.1 (AP_SDO/AP_AD0); also elsewhere on the board
/Data Logging/MISO4: U2.1 (AP_SDO/AP_AD0); also elsewhere on the board
/Data Logging/MOSI1: U4.14 (AP_SDA/AP_SDIO/AP_SDI); also elsewhere on the board
/Data Logging/MOSI2: U1.14 (AP_SDA/AP_SDIO/AP_SDI); also elsewhere on the board
/Data Logging/MOSI3: U3.14 (AP_SDA/AP_SDIO/AP_SDI); also elsewhere on the board
/Data Logging/MOSI4: U2.14 (AP_SDA/AP_SDIO/AP_SDI); also elsewhere on the board
/Data Logging/SCK1: U4.13 (AP_SCL/AP_SCLK); also elsewhere on the board
/Data Logging/SCK2: U1.13 (AP_SCL/AP_SCLK); also elsewhere on the board
/Data Logging/SCK3: U3.13 (AP_SCL/AP_SCLK); also elsewhere on the board
/Data Logging/SCK4: U2.13 (AP_SCL/AP_SCLK); also elsewhere on the board
/Data Logging/SET: C19.1, R1.1, U5.7 (SET)
/Data Logging/Vout_LT3045: C18.1, JP1.1 (A), U5.6 (PGFB), U5.9 (OUTS), U5.10 (OUT)
/Data Logging/Vout_XC6206: C21.1, JP2.1 (A), U9.2 (Vout)
GND: C1.2, C2.2, C3.2, C4.2, C5.2, C6.2, C7.2, C8.2, C9.2, C10.2, C11.2, C12.2, C13.2, C14.2, C15.2, C16.2, C17.2, C18.2, C19.2, C20.2, C21.2, R2.2, U1.2 (RESV), U1.3 (RESV), U1.6 (GND), U1.7 (RESV), U1.10 (RESV), U1.11 (RESV), U2.2 (RESV), U2.3 (RESV), U2.6 (GND), U2.7 (RESV), U2.10 (RESV), U2.11 (RESV), U3.2 (RESV), U3.3 (RESV), U3.6 (GND), U3.7 (RESV), U3.10 (RESV), U3.11 (RESV), U4.2 (RESV), U4.3 (RESV), U4.6 (GND), U4.7 (RESV), U4.10 (RESV), U4.11 (RESV), U5.5 (ILIM), U5.8 (GND), U5.11 (GND), U9.1 (GND); also elsewhere on the board
unnamed: C1.1, C2.1, C3.1, C4.1, C5.1, C6.1, C7.1, C8.1, C9.1, C10.1, C11.1, C12.1, C13.1, C14.1, C15.1, C16.1, JP1.2 (B), JP2.2 (B), JP3.2 (B_2), U1.5 (VDDIO), U1.8 (VDD), U2.5 (VDDIO), U2.8 (VDD), U3.5 (VDDIO), U3.8 (VDD), U4.5 (VDDIO), U4.8 (VDD)
unnamed: R1.2, R2.1

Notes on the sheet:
IMU Array - 4x ICM-42688-P
High Noise LDO XC6206
Ultra Low Noise LDO LT3045
